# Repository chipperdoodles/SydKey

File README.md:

# SydKey
Kicad files for a 4x6 numbpad using bluefruit 32u4 feather

### Design
This is a dead simple design is to make a bluetooth/qmk compatible number pad with small oled screen. It has 4 function keys and a full number pad layout underneath, it does not support alps switches or alternate layouts.

It was designed with my home workflow in mind. This involves being etched via tiny cheap cnc engraver, hand soldered and then programmed via QMK. Trace width and pad shapes were messed with to make hand soldering more forgivable. It's also designed with the intention of one side being traced and the other side being hand wired, I found in my struggles with my aligning front and back designs in the process.

### BOM
* 6x4 Copper Clad Board
* Diodes
* Cherry Mx compatible switches
* i2c Oled (I used the adafruit 128x64)
* Adafruit Bluefruit 32u4 Feather

### Programming
The board is programmed using the open source firmware QMK, its quite excellent and though I may not be a great programmer, their documentation covers the essential basics and with examples I pulled together some code to get it functioning. However, I know someone can do much better! See more in the QMK code folder.

### Versioning
* V.02 - Added pull up resistors however I think I did them wrong.
* V.01 - Functioning prototype

### TODO
* Fix old kicad diode in schematics so the proper pin is selected in the pcb. Currently on the pcb the diode direction is reversed from how you actually want to solder them.
* Program ios/android shortcuts/clean up default keymap

### Resources
* Kicad
* Regack's 4x6 numbpad
* adafruit kicad lib
* teensy kicad lib
* geekhack forums
* input club design files
* deskauthority wiki

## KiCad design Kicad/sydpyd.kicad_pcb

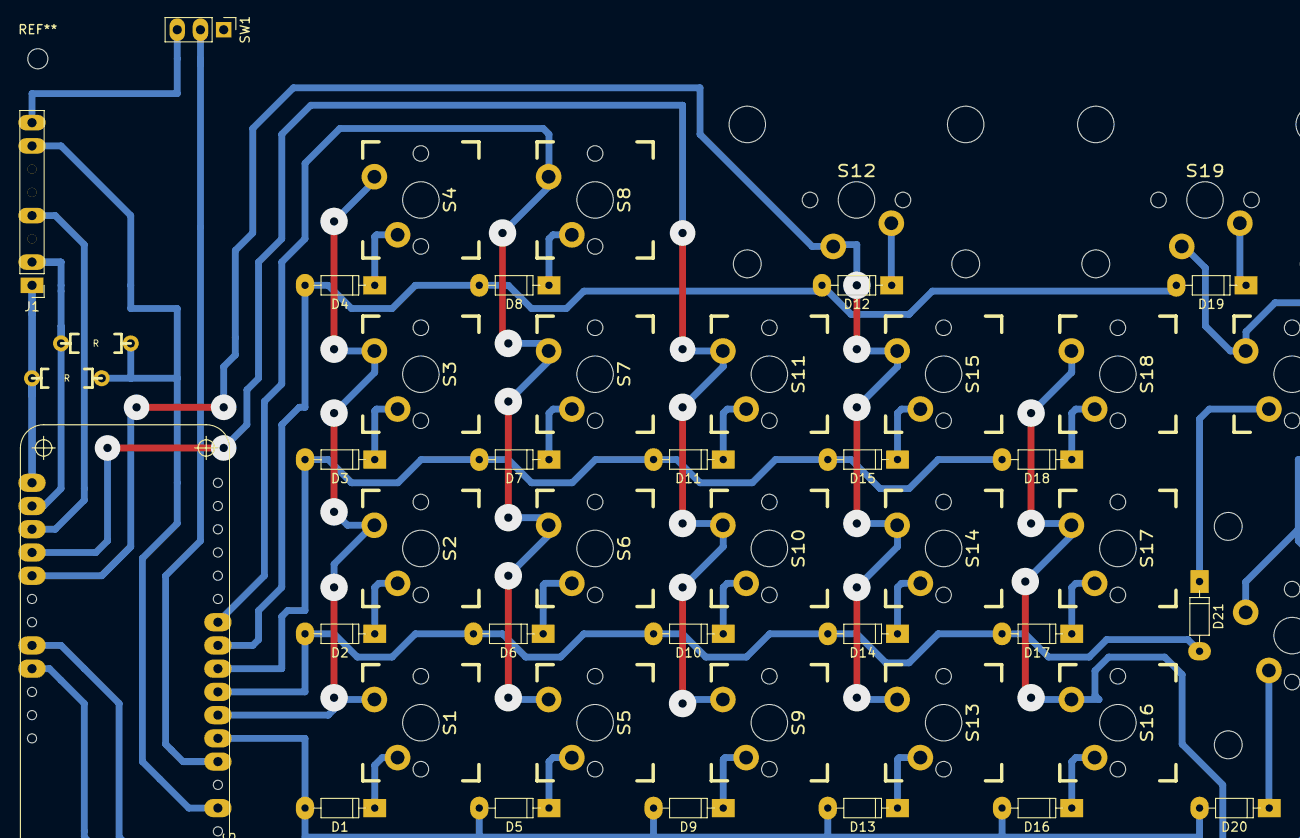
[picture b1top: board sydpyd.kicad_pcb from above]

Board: 2 copper layers, 47 parts (0 on the bottom side), 37 nets.

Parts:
D1, D2, D3, D4, D5, D6, D7, D8, D9, D10, D11, D12, D13, D14, D15, D16, D17, D18, D19, D20, D21: 1N4148; D_DO-35_SOD27_P7.62mm_Horizontal
J1: OLED; Socket_Strip_Straight_1x08_Pitch2.54mm
MS1: FEATHERWING
R1, R2: R; Resistor_THT
S1, S2, S3, S4, S5, S6, S7, S8, S9, S10, S11, S13, S14, S15, S16, S17, S18, S21: MX1A; CHERRY_PCB_100H
S12, S19, S20: MX1A; CHERRY_PCB_200H
SW1: SW_DPDT_x2; Socket_Strip_Straight_1x03_Pitch2.54mm

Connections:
/SCL: J1.2, MS1.18, R2.2
/SDA: J1.1, MS1.17, R1.1
/col1: D1.2, D5.2, D9.2, D13.2, D16.2, D20.2, MS1.5
/col2: D2.2, D6.2, D10.2, D14.2, D17.2, D21.2, MS1.7
/col3: D3.2, D7.2, D11.2, D15.2, D18.2, MS1.8
/col4: D4.2, D8.2, D12.2, D19.2, MS1.9
/row1: MS1.6, S1.1, S2.1, S3.1, S4.1
/row2: MS1.10, S5.1, S6.1, S7.1, S8.1
/row3: MS1.20, S9.1, S10.1, S11.1
/row4: MS1.21, S12.1, S13.1, S14.1, S15.1
/row5: MS1.24, S16.1, S17.1, S18.1
/row6: MS1.25, S19.1, S20.1, S21.1
/~RES~: J1.4, MS1.19
GND: MS1.4, SW1.2
unnamed: D1.1, S1.2
unnamed: D2.1, S2.2
unnamed: D3.1, S3.2
unnamed: D4.1, S4.2
unnamed: D5.1, S5.2
unnamed: D6.1, S6.2
unnamed: D7.1, S7.2
unnamed: D8.1, S8.2
unnamed: D9.1, S9.2
unnamed: D10.1, S10.2
unnamed: D11.1, S11.2
unnamed: D12.1, S12.2
unnamed: D13.1, S13.2
unnamed: D14.1, S14.2
unnamed: D15.1, S15.2
unnamed: D16.1, S16.2
unnamed: D17.1, S17.2
unnamed: D18.1, S18.2
unnamed: D19.1, S19.2
unnamed: D20.1, S20.2
unnamed: D21.1, S21.2
unnamed: J1.8, SW1.3
VCC: J1.7, MS1.2, R1.2, R2.1

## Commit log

2018-07-12 Initial readme
2018-07-12 Deleting
2018-07-12 build file
2018-07-22 Initial Kicad File upload
2018-07-24 Update with photos and readme
2018-07-24 QMK code uploaded
2019-02-08 minoor changes
